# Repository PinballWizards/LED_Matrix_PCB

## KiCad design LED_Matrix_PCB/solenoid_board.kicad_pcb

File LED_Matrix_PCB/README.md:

# pcb_solenoid_board
KiCAD PCB files for Solenoid Node Board

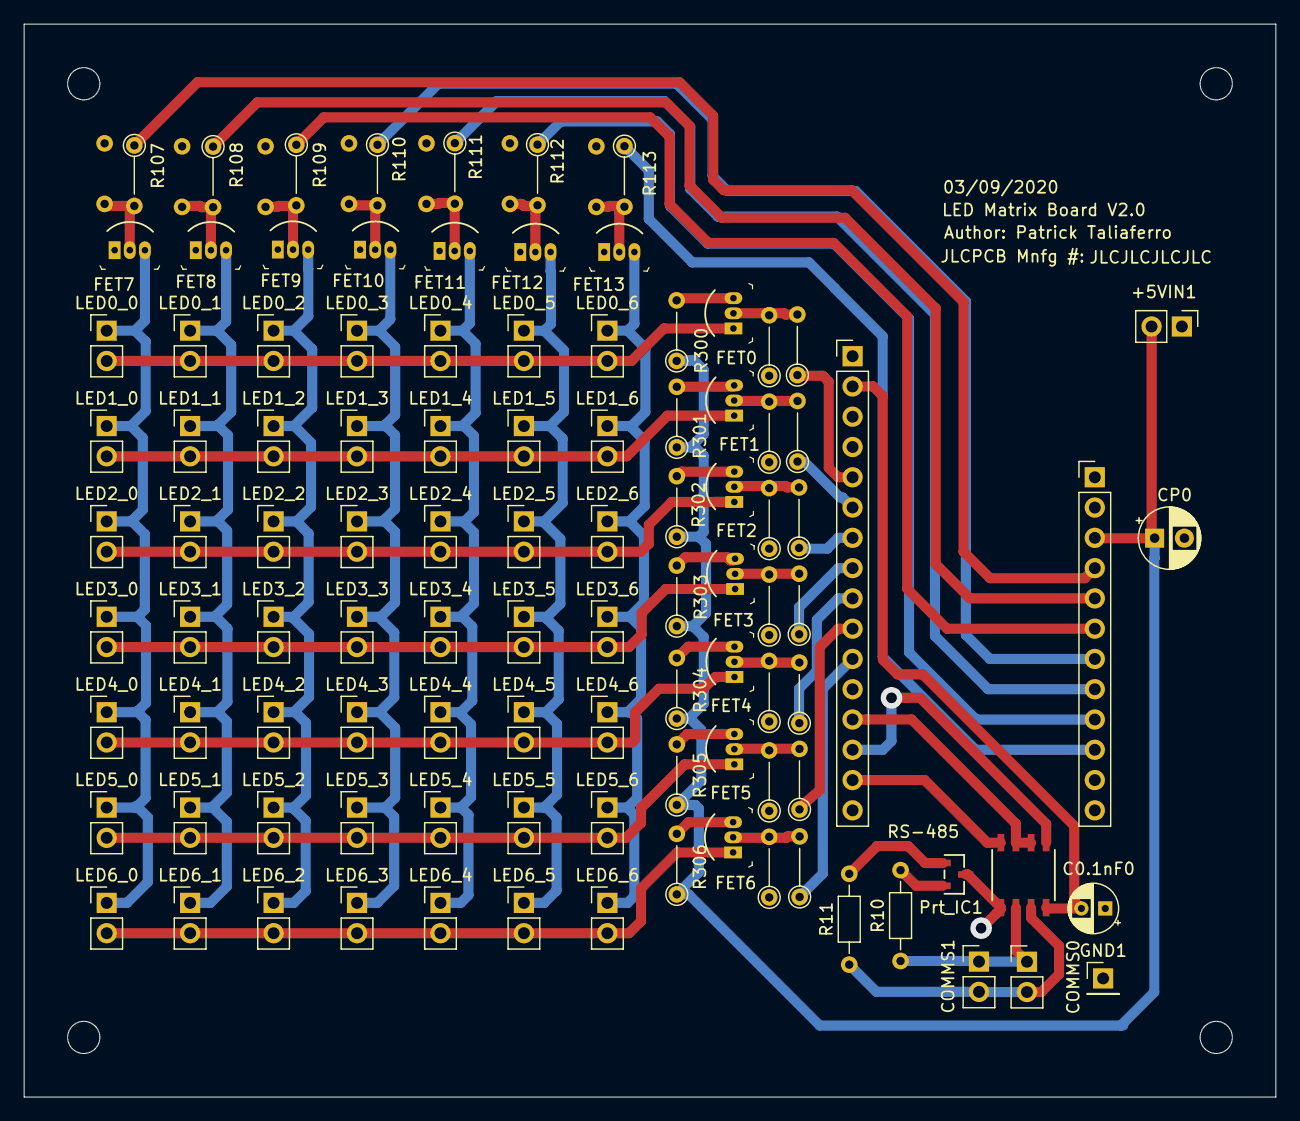
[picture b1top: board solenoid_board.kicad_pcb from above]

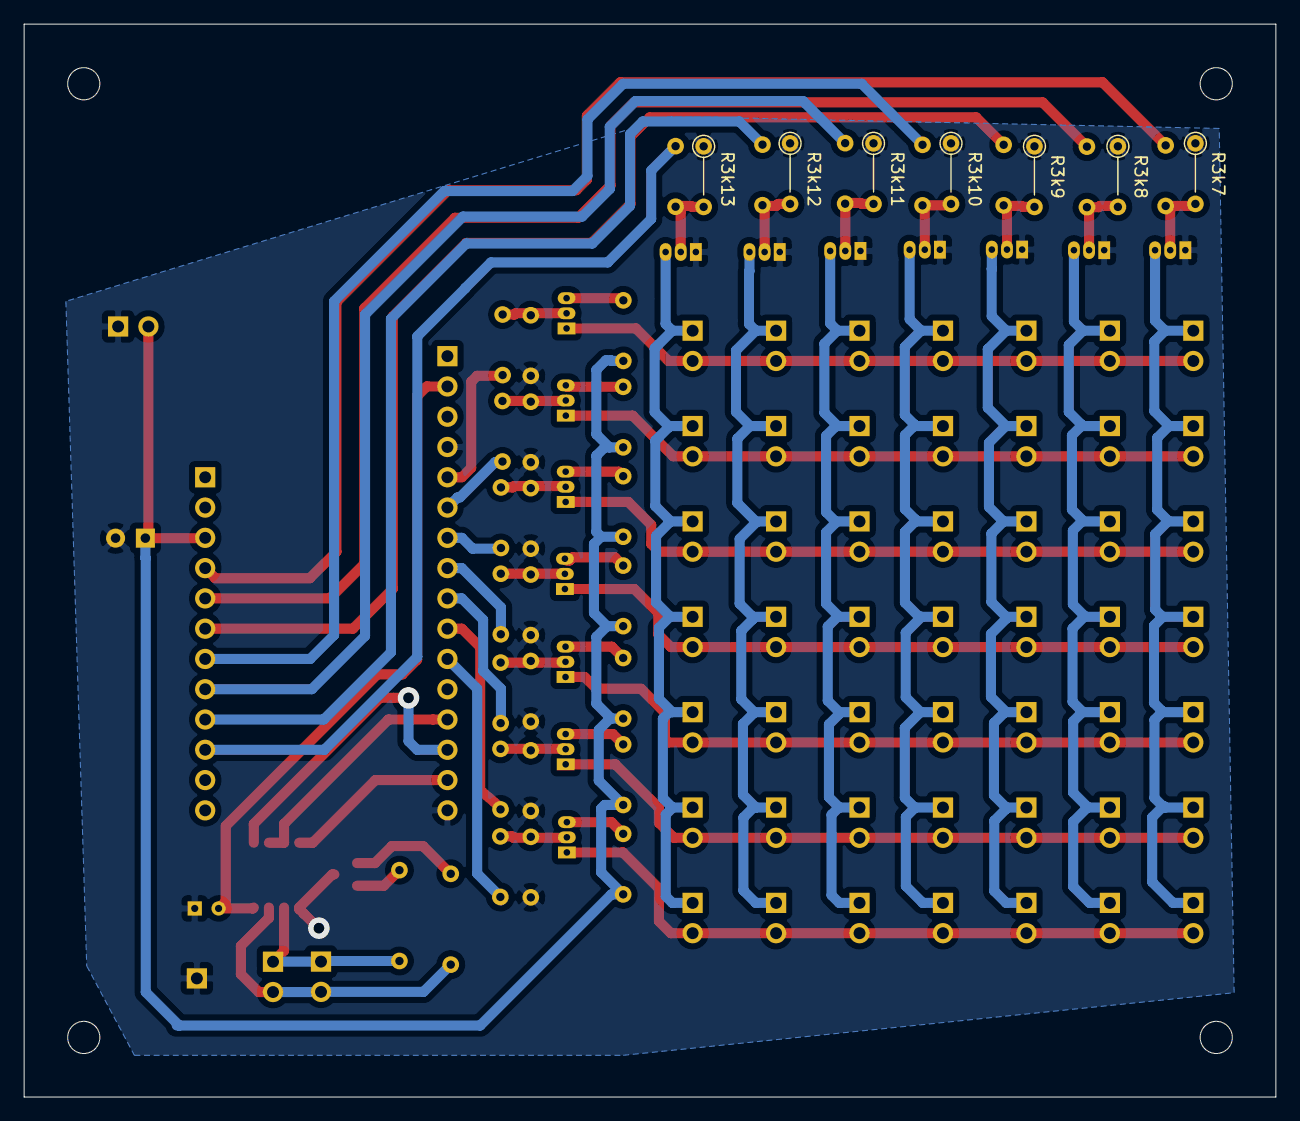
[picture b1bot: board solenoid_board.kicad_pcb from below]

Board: 2 copper layers, 105.0 x 90.0 mm, 110 parts (7 on the bottom side), 59 nets.

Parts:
+5VIN1: Conn_01x02; PinHeader_1x02_P2.54mm_Vertical
C0.1nF0: 0.1 nF; CP_Radial_D4.0mm_P2.00mm
COMMS0, COMMS1: Conn_01x02; PinHeader_1x02_P2.54mm_Vertical
CP0: CP; CP_Radial_D5.0mm_P2.50mm
FET0, FET1, FET2, FET3, FET4, FET5, FET6, FET7, FET8, FET9, FET10, FET11, FET12, FET13: 2N7000; TO-92-3
GND1: Conn_01x01; PinHeader_1x01_P2.54mm_Vertical
J2: MCU_LEFT_LEGS; PinHeader_1x16_P2.54mm_Vertical
J3: MCU_RIGHT_LEGS; PinHeader_1x12_P2.54mm_Vertical
LED0_0, LED0_1, LED0_2, LED0_3, LED0_4, LED0_5, LED0_6, LED1_0, LED1_1, LED1_2, LED1_3, LED1_4, LED1_5, LED1_6, LED2_0, LED2_1, LED2_2, LED2_3, LED2_4, LED2_5, LED2_6, LED3_0, LED3_1, LED3_2, LED3_3, LED3_4, LED3_5, LED3_6, LED4_0, LED4_1, LED4_2, LED4_3, LED4_4, LED4_5, LED4_6, LED5_0, LED5_1, LED5_2, LED5_3, LED5_4, LED5_5, LED5_6, LED6_0, LED6_1, LED6_2, LED6_3, LED6_4, LED6_5, LED6_6: Conn_01x02; PinHeader_1x02_P2.54mm_Vertical
Prt_IC1: CDSOT23-SM712
R3k0, R3k1, R3k2, R3k3, R3k4, R3k5, R3k6, R3k7, R3k8, R3k9, R3k10, R3k11, R3k12, R3k13: 3k; R_Axial_DIN0204_L3.6mm_D1.6mm_P5.08mm_Vertical
R10, R11: 10; R_Axial_DIN0204_L3.6mm_D1.6mm_P7.62mm_Horizontal
R100, R102, R103, R104, R105, R106, R107, R108, R109, R110, R111, R112, R113: 100; R_Axial_DIN0204_L3.6mm_D1.6mm_P5.08mm_Vertical
R101: 10; R_Axial_DIN0204_L3.6mm_D1.6mm_P5.08mm_Vertical
R300, R301, R302, R303, R304, R305, R306: 300; R_Axial_DIN0204_L3.6mm_D1.6mm_P5.08mm_Vertical
RS-485: SN65HVD72DR

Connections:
+3V3: C0.1nF0.2, J2.2, RS-485.8
+5V: +5VIN1.2, CP0.1, J3.3, R300.1, R301.1, R302.1, R303.1, R304.1, R305.1, R306.1
/A: COMMS0.1, COMMS1.1, R10.1, RS-485.6
/A0: J2.5, R100.1
/A1: J2.6, R101.1
/A2: J2.7, R102.1
/A3: J2.8, R103.1
/A4: J2.9, R104.1
/A5: J2.10, R105.1
/B: COMMS0.2, COMMS1.2, R11.1, RS-485.7
/COL0: FET7.3, LED0_0.1, LED1_0.1, LED2_0.1, LED3_0.1, LED4_0.1, LED5_0.1, LED6_0.1
/COL1: FET8.3, LED0_1.1, LED1_1.1, LED2_1.1, LED3_1.1, LED4_1.1, LED5_1.1, LED6_1.1
/COL2: FET9.3, LED0_2.1, LED1_2.1, LED2_2.1, LED3_2.1, LED4_2.1, LED5_2.1, LED6_2.1
/COL3: FET10.3, LED0_3.1, LED1_3.1, LED2_3.1, LED3_3.1, LED4_3.1, LED5_3.1, LED6_3.1
/COL4: FET11.3, LED0_4.1, LED1_4.1, LED2_4.1, LED3_4.1, LED4_4.1, LED5_4.1, LED6_4.1
/COL5: FET12.3, LED0_5.1, LED1_5.1, LED2_5.1, LED3_5.1, LED4_5.1, LED5_5.1, LED6_5.1
/COL6: FET13.3, LED0_6.1, LED1_6.1, LED2_6.1, LED3_6.1, LED4_6.1, LED5_6.1, LED6_6.1
/D5: J3.10, R113.1
/D6: J3.9, R112.1
/D9: J3.8, R111.1
/D10: J3.7, R110.1
/D11: J3.6, R109.1
/D12: J3.5, R108.1
/D13: J3.4, R107.1
/MISO: J2.13, RS-485.2, RS-485.3
/ROW0: FET0.1, LED0_0.2, LED0_1.2, LED0_2.2, LED0_3.2, LED0_4.2, LED0_5.2, LED0_6.2
/ROW1: FET1.1, LED1_0.2, LED1_1.2, LED1_2.2, LED1_3.2, LED1_4.2, LED1_5.2, LED1_6.2
/ROW2: FET2.1, LED2_0.2, LED2_1.2, LED2_2.2, LED2_3.2, LED2_4.2, LED2_5.2, LED2_6.2
/ROW3: FET3.1, LED3_0.2, LED3_1.2, LED3_2.2, LED3_3.2, LED3_4.2, LED3_5.2, LED3_6.2
/ROW4: FET4.1, LED4_0.2, LED4_1.2, LED4_2.2, LED4_3.2, LED4_4.2, LED4_5.2, LED4_6.2
/ROW5: FET5.1, LED5_0.2, LED5_1.2, LED5_2.2, LED5_3.2, LED5_4.2, LED5_5.2, LED5_6.2
/ROW6: FET6.1, LED6_0.2, LED6_1.2, LED6_2.2, LED6_3.2, LED6_4.2, LED6_5.2, LED6_6.2
/RX0: J2.14, RS-485.1
/SCK: J2.11, R106.1
/TX1: J2.15, RS-485.4
GND: +5VIN1.1, C0.1nF0.1, CP0.2, FET7.1, FET8.1, FET9.1, FET10.1, FET11.1, FET12.1, FET13.1, GND1.1, J2.4, J2.16, Prt_IC1.3, R3k0.1, R3k1.1, R3k2.1, R3k3.1, R3k4.1, R3k5.1, R3k6.1, R3k7.1, R3k8.1, R3k9.1, R3k10.1, R3k11.1, R3k12.1, R3k13.1, RS-485.5
unnamed: FET0.2, R3k0.2, R100.2
unnamed: FET0.3, R300.2
unnamed: FET1.2, R3k1.2, R101.2
unnamed: FET1.3, R301.2
unnamed: FET2.2, R3k2.2, R102.2
unnamed: FET2.3, R302.2
unnamed: FET3.2, R3k3.2, R103.2
unnamed: FET3.3, R303.2
unnamed: FET4.2, R3k4.2, R104.2
unnamed: FET4.3, R304.2
unnamed: FET5.2, R3k5.2, R105.2
unnamed: FET5.3, R305.2
unnamed: FET6.2, R3k6.2, R106.2
unnamed: FET6.3, R306.2
unnamed: FET7.2, R3k7.2, R107.2
unnamed: FET8.2, R3k8.2, R108.2
unnamed: FET9.2, R3k9.2, R109.2
unnamed: FET10.2, R3k10.2, R110.2
unnamed: FET11.2, R3k11.2, R111.2
unnamed: FET12.2, R3k12.2, R112.2
unnamed: FET13.2, R3k13.2, R113.2
unnamed: Prt_IC1.1, R11.2
unnamed: Prt_IC1.2, R10.2

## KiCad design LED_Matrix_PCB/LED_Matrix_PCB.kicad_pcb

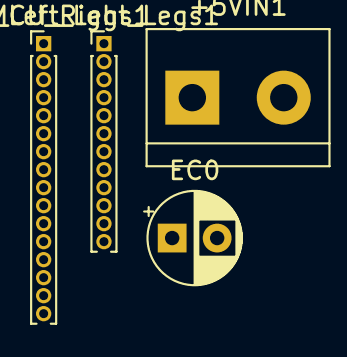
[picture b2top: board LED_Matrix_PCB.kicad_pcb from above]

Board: 2 copper layers, 4 parts (0 on the bottom side), 2 nets, no tracks yet.

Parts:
+5VIN1: Screw_Terminal_01x02; TerminalBlock_bornier-2_P5.08mm
EC0: CP; CP_Radial_D5.0mm_P2.50mm
MCU_Left_Legs1: Conn_01x16_Female; PinHeader_1x16_P1.00mm_Vertical
MCU_Right_Legs1: Conn_01x12_Female; PinHeader_1x12_P1.00mm_Vertical

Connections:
+5V: +5VIN1.1, EC0.1, MCU_Right_Legs1.3
GND: +5VIN1.2, EC0.2, MCU_Left_Legs1.4, MCU_Left_Legs1.16

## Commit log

2020-02-07 Placed the MCU and 5V input terminal on the schematic. Need to change the footprint on the pin headers to match that of the solenoid board's MCU.
2020-02-07 Imported the solenoid board schematic and pcb layout and then erased application specifics. Added 81 1x2 terminal connections for a 9x9 LED Matrix with 1 330 ohm resistor on each column pin. The pcb 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
2020-02-09 Laid footprint geometry. Need to add a capacitor on the RS-485 Transciever.
2020-02-09 Routed 90% of wires, still need to re-order the column pin masking to better complement the routing.
2020-02-09 Placed finishing touches on V1.0
2020-02-09 Finished BOM
2020-02-11 Updated hyperlink, shave 50% off the per-board price by changing 2-pin terminal block suppliers.
2020-02-11 Changed footprints for resistors, changed resistor suppliers, and re-routed wires. Need to add mounting holes and clean for ordering.
2020-02-13 Updated the .gbr files.
2020-02-13 Added Mounting Holes
2020-02-22 Changed BOM significantly. Need to swap out screw terminals for 7x7 2-pin headers on schematic. Need to change geometry of the board. Need to change Resistor Footprint. May want to start a new projec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
2020-02-23 Forgot to close files before pushing.
2020-02-23 Fixed the connections of the downstream MOSFETS. WOrked on geometry, sorted out footprints.
2020-02-23 Cleaned geometry on layout. Routed a number of wires. Only a little bit of routing left.
2020-02-24 Finished routing. Done. Ready to be merged. V2 Complete.
2020-02-25 Moved Silk Screen and other
2020-02-25 Changed mosfet circuitry.
2020-03-09 Added a pull down resistor and re-routed. Also, updated BOM.

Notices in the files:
parts and their libraries:
Copyright 2016 Accelerated Designs. All rights reserved.
